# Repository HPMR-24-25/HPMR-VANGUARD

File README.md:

# HPMR KiCad Flight Computer Project

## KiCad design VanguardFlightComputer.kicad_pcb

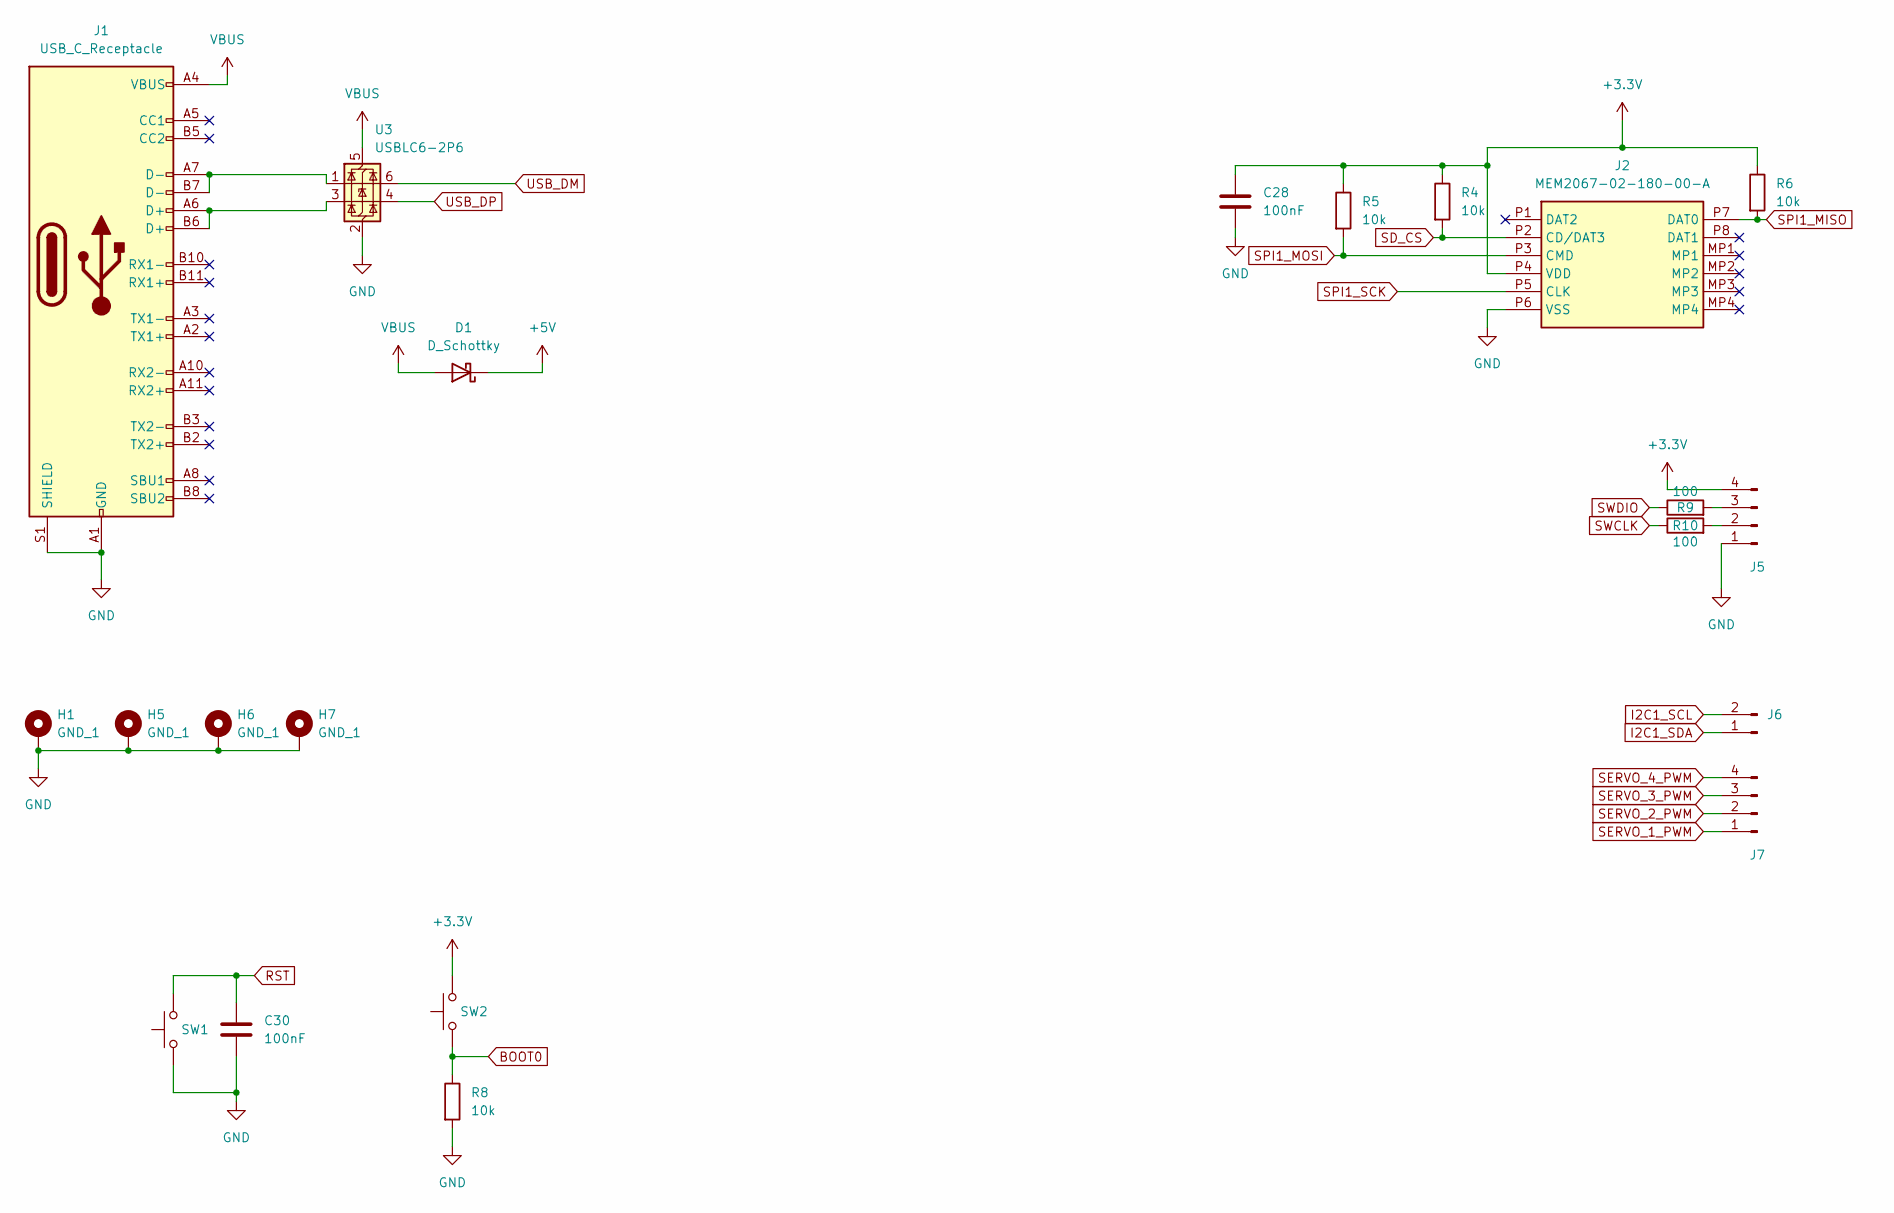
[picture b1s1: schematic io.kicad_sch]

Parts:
C28, C30: 100nF; C_0402_1005Metric
D1: D_Schottky; D_0402_1005Metric
H1, H5, H6, H7: GND_1; MountingHole_2.2mm_M2_DIN965_Pad_TopBottom
J1: USB_C_Receptacle; USB_C_Receptacle_Molex_105450-0101
J2: MEM2067-02-180-00-A; MEM20670218000A; Manufacturer_Part_Number MEM2067-02-180-00-A; Mouser Part Number 640-MEM20670218000A
J5, J7: Conn_01x04_Pin; PinSocket_1x04_P2.54mm_Vertical
J6: Conn_01x02_Pin; PinHeader_1x02_P2.54mm_Vertical
R4, R5, R6, R8: 10k; R_0402_1005Metric
R9, R10: 100; R_0402_1005Metric
SW1, SW2: SW_Push; SW_SPST_PTS810
U3: USBLC6-2P6; SOT-666

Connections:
+3.3V: C28.1, J2.P4 (VDD), J5.4, R4.1, R5.1, R6.1, SW2.2; also elsewhere on the board
+5V: D1.1 (K); also elsewhere on the board
BOOT0: R8.1, SW2.1; also elsewhere on the board
GND: C28.2, C30.2, H1.MP, H5.MP, H6.MP, H7.MP, J1.A1 (GND), J1.A12 (GND), J1.B1 (GND), J1.B12 (GND), J1.S1 (SHIELD), J2.P6 (VSS), J5.1, R8.2, SW1.1, U3.2 (GND); also elsewhere on the board
I2C1_SCL: J6.2; also elsewhere on the board
I2C1_SDA: J6.1; also elsewhere on the board
unnamed: J1.A6 (D+), J1.B6 (D+), U3.3 (I/O2)
unnamed: J1.A7 (D-), J1.B7 (D-), U3.1 (I/O1)
unnamed: J5.2, R10.2
unnamed: J5.3, R9.2
RST: C30.1, SW1.2; also elsewhere on the board
SD_CS: J2.P2 (CD/DAT3), R4.2; also elsewhere on the board
SERVO_1_PWM: J7.1; also elsewhere on the board
SERVO_2_PWM: J7.2; also elsewhere on the board
SERVO_3_PWM: J7.3; also elsewhere on the board
SERVO_4_PWM: J7.4; also elsewhere on the board
SPI1_MISO: J2.P7 (DAT0), R6.2; also elsewhere on the board
SPI1_MOSI: J2.P3 (CMD), R5.2; also elsewhere on the board
SPI1_SCK: J2.P5 (CLK); also elsewhere on the board
SWCLK: R10.1; also elsewhere on the board
SWDIO: R9.1; also elsewhere on the board
USB_DM: U3.6 (I/O1); also elsewhere on the board
USB_DP: U3.4 (I/O2); also elsewhere on the board
VBUS: D1.2 (A), J1.A4 (VBUS), J1.A9 (VBUS), J1.B4 (VBUS), J1.B9 (VBUS), U3.5 (VBUS)

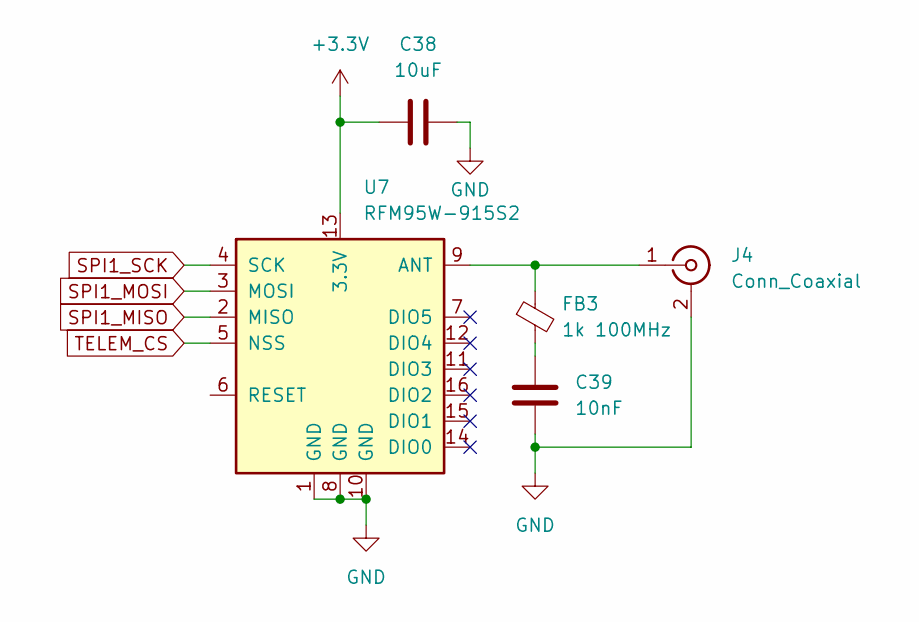
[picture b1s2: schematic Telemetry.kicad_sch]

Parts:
C38: 10uF; C_0402_1005Metric
C39: 10nF; C_0402_1005Metric
FB3: 1k 100MHz; C_0603_1608Metric
J4: Conn_Coaxial; U.FL_Hirose_U.FL-R-SMT-1_Vertical
U7: RFM95W-915S2; HOPERF_RFM9XW_SMD

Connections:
+3.3V: C38.1, U7.13 (3.3V); also elsewhere on the board
GND: C38.2, C39.2, J4.2 (Ext), U7.1 (GND), U7.8 (GND), U7.10 (GND); also elsewhere on the board
unnamed: C39.1, FB3.2
unnamed: FB3.1, J4.1 (In), U7.9 (ANT)
SPI1_MISO: U7.2 (MISO); also elsewhere on the board
SPI1_MOSI: U7.3 (MOSI); also elsewhere on the board
SPI1_SCK: U7.4 (SCK); also elsewhere on the board
TELEM_CS: U7.5 (NSS); also elsewhere on the board

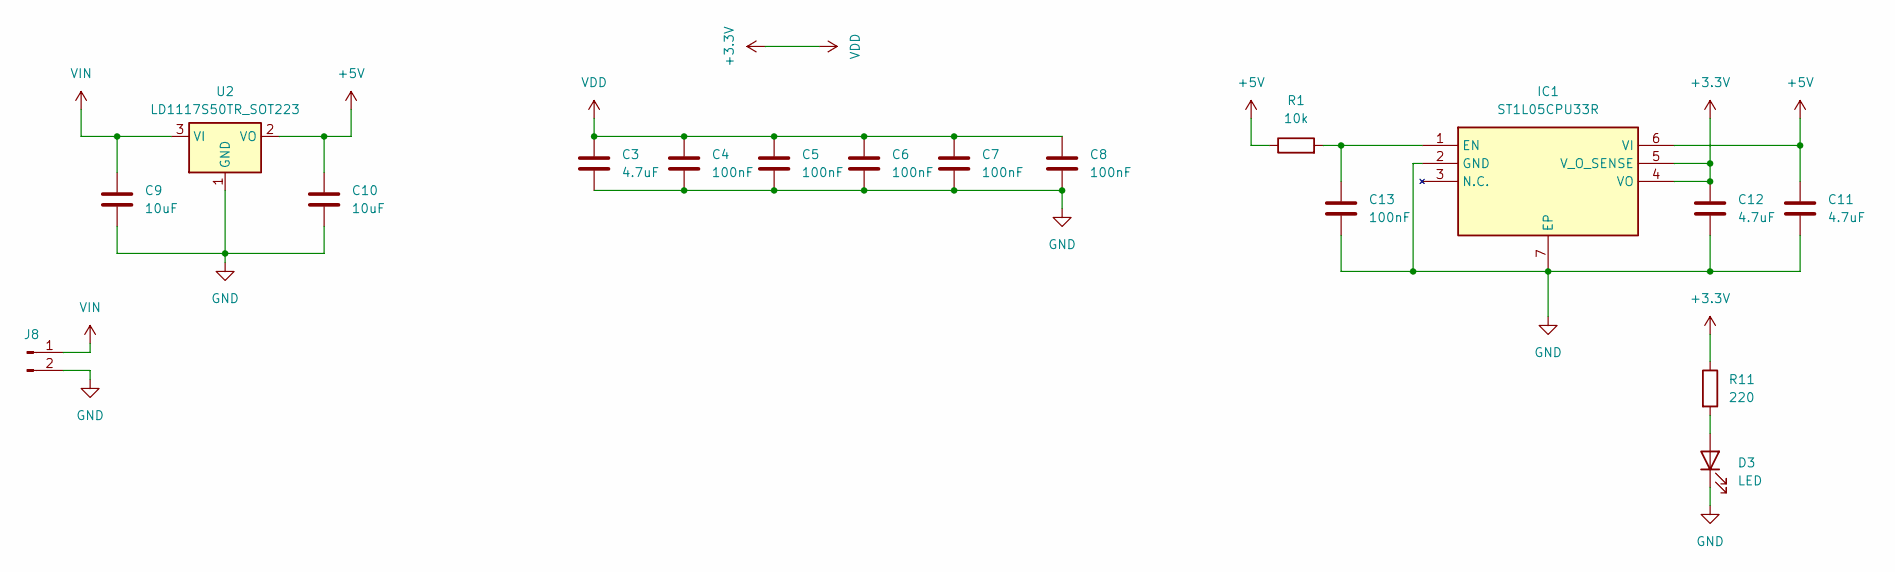
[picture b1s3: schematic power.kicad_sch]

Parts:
C3, C11, C12: 4.7uF; C_0402_1005Metric
C4, C5, C6, C7, C8, C13: 100nF; C_0402_1005Metric
C9, C10: 10uF; C_0603_1608Metric
D3: LED; LED_0603_1608Metric
IC1: ST1L05CPU33R; SON95P300X300X100-7N-D; Manufacturer_Part_Number ST1L05CPU33R; Mouser Part Number 511-ST1L05CPU33R
J8: Conn_01x02_Pin; PinHeader_1x02_P2.54mm_Vertical
R1: 10k; R_0603_1608Metric
R11: 220; R_0402_1005Metric
U2: LD1117S50TR_SOT223; SOT-223-3_TabPin2

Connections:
+3.3V: C3.1, C4.1, C5.1, C6.1, C7.1, C8.1, C12.1, IC1.4 (VO), IC1.5 (V_O_SENSE), R11.1; also elsewhere on the board
+5V: C10.1, C11.1, IC1.6 (VI), R1.1, U2.2 (VO); also elsewhere on the board
GND: C3.2, C4.2, C5.2, C6.2, C7.2, C8.2, C9.2, C10.2, C11.2, C12.2, C13.2, D3.1 (K), IC1.2 (GND), IC1.7 (EP), J8.2, U2.1 (GND); also elsewhere on the board
unnamed: D3.2 (A), R11.2
unnamed: C13.1, IC1.1 (EN), R1.2
VIN: C9.1, J8.1, U2.3 (VI)

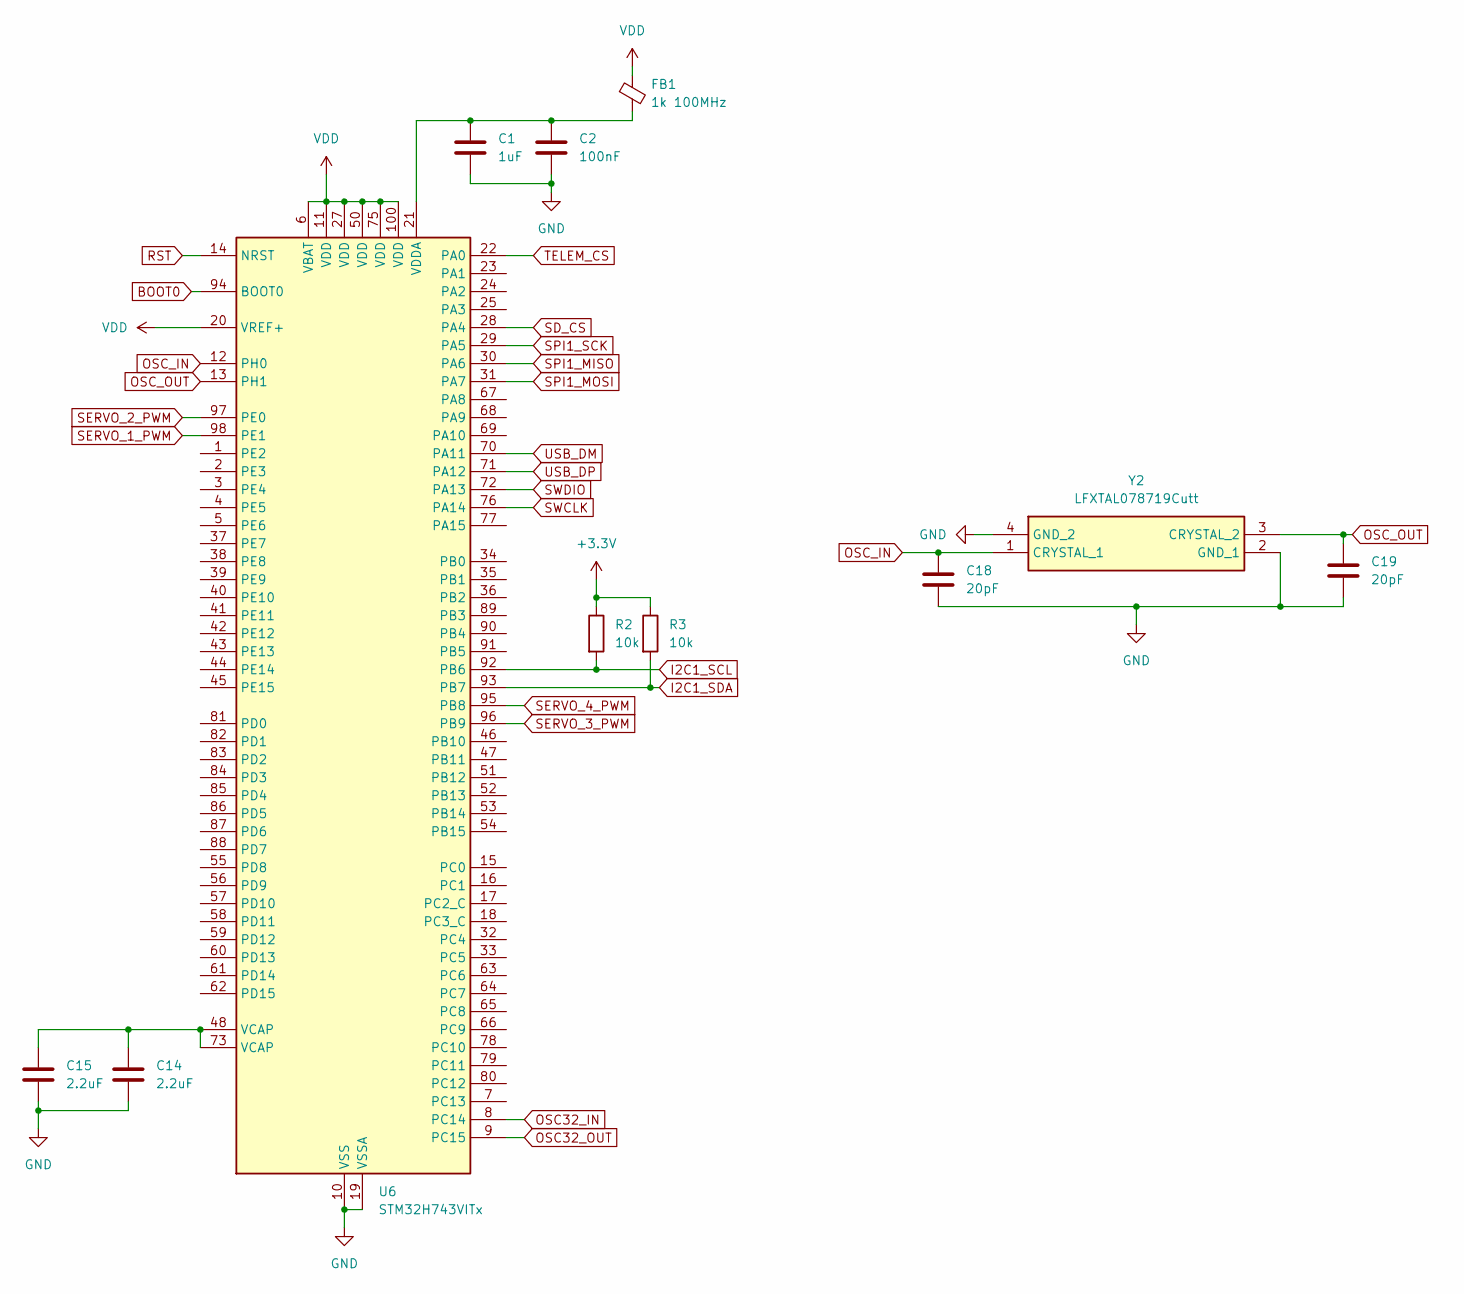
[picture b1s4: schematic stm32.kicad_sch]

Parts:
C1: 1uF; C_0402_1005Metric
C2: 100nF; C_0402_1005Metric
C14, C15: 2.2uF; C_0402_1005Metric
C18, C19: 20pF; C_0402_1005Metric
FB1: 1k 100MHz; C_0603_1608Metric
R2, R3: 10k; R_0402_1005Metric
U6: STM32H743VITx; LQFP-100_14x14mm_P0.5mm
Y2: LFXTAL078719Cutt; Manufacturer_Part_Number LFXTAL078719Cutt; Mouser Part Number 449-LFXTAL078719CUTT

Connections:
+3.3V: FB1.1, R2.1, R3.1, U6.6 (VBAT), U6.11 (VDD), U6.20 (VREF+), U6.27 (VDD), U6.50 (VDD), U6.75 (VDD), U6.100 (VDD); also elsewhere on the board
BOOT0: U6.94 (BOOT0); also elsewhere on the board
GND: C1.2, C2.2, C14.2, C15.2, C18.1, C19.1, U6.10 (VSS), U6.19 (VSSA), U6.26 (VSS), U6.49 (VSS), U6.74 (VSS), U6.99 (VSS), Y2.2 (GND_1), Y2.4 (GND_2); also elsewhere on the board
I2C1_SCL: R2.2, U6.92 (PB6); also elsewhere on the board
I2C1_SDA: R3.2, U6.93 (PB7); also elsewhere on the board
unnamed: C14.1, C15.1, U6.48 (VCAP), U6.73 (VCAP)
unnamed: C1.1, C2.1, FB1.2, U6.21 (VDDA)
OSC32_IN: U6.8 (PC14)
OSC32_OUT: U6.9 (PC15)
OSC_IN: C18.2, U6.12 (PH0), Y2.1 (CRYSTAL_1)
OSC_OUT: C19.2, U6.13 (PH1), Y2.3 (CRYSTAL_2)
RST: U6.14 (NRST); also elsewhere on the board
SD_CS: U6.28 (PA4); also elsewhere on the board
SERVO_1_PWM: U6.98 (PE1); also elsewhere on the board
SERVO_2_PWM: U6.97 (PE0); also elsewhere on the board
SERVO_3_PWM: U6.96 (PB9); also elsewhere on the board
SERVO_4_PWM: U6.95 (PB8); also elsewhere on the board
SPI1_MISO: U6.30 (PA6); also elsewhere on the board
SPI1_MOSI: U6.31 (PA7); also elsewhere on the board
SPI1_SCK: U6.29 (PA5); also elsewhere on the board
SWCLK: U6.76 (PA14); also elsewhere on the board
SWDIO: U6.72 (PA13); also elsewhere on the board
TELEM_CS: U6.22 (PA0); also elsewhere on the board
USB_DM: U6.70 (PA11); also elsewhere on the board
USB_DP: U6.71 (PA12); also elsewhere on the board

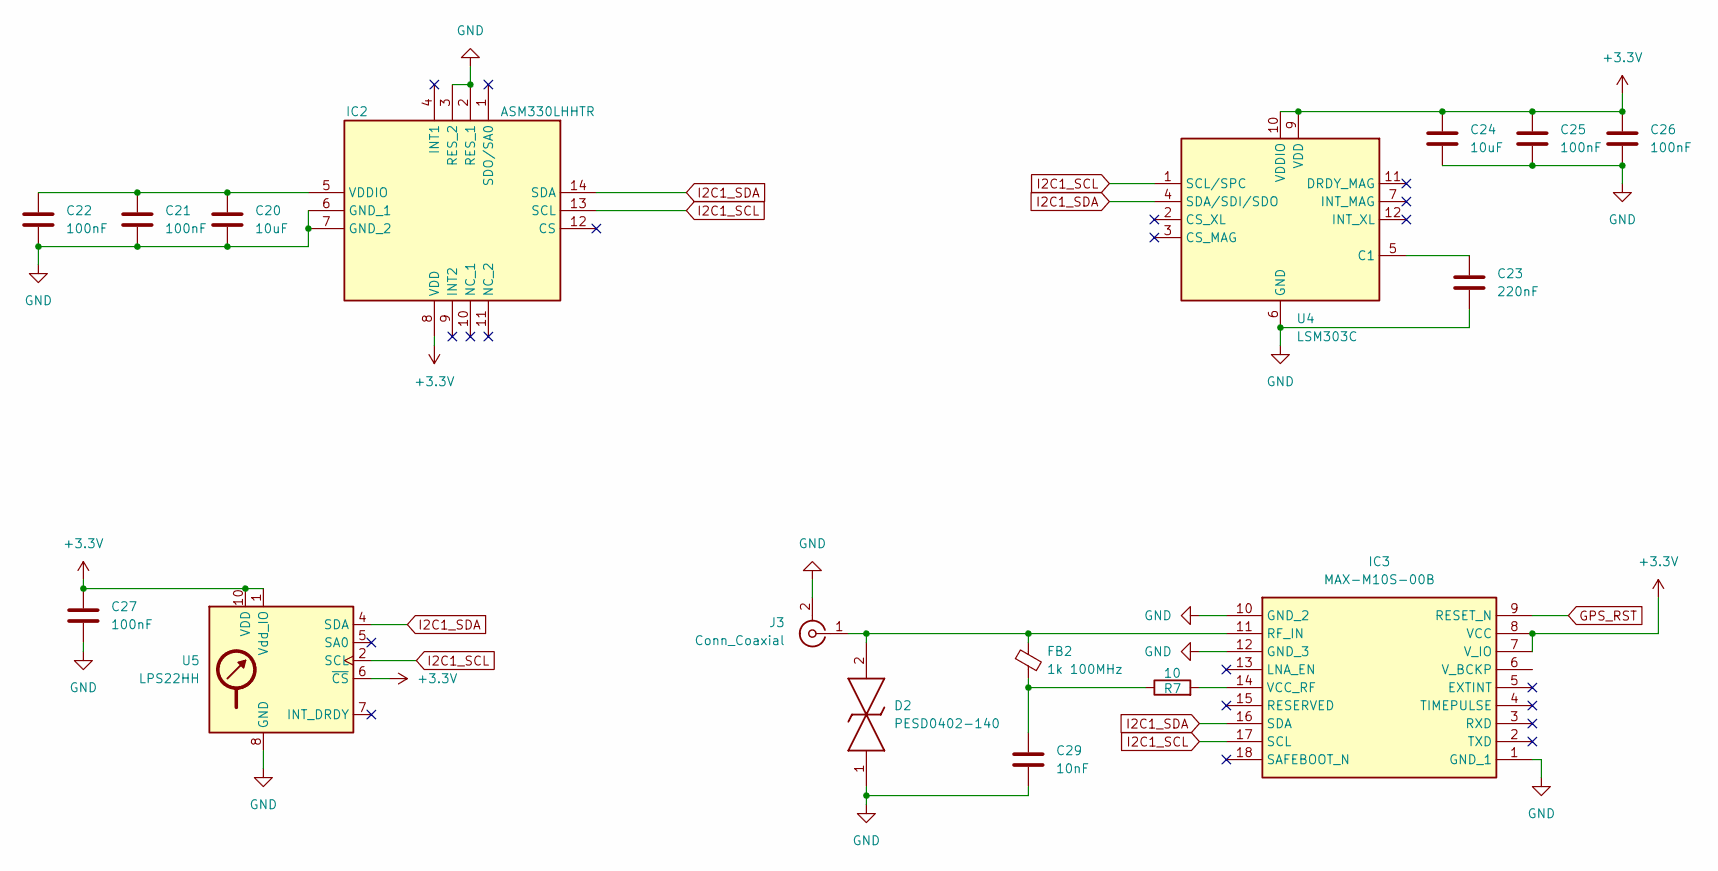
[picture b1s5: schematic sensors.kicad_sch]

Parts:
C20, C24: 10uF; C_0402_1005Metric
C21, C22, C25, C26, C27: 100nF; C_0402_1005Metric
C23: 220nF; C_0402_1005Metric
C29: 10nF; C_0402_1005Metric
D2: PESD0402-140; DIONC1005X43N; Mouser Part Number 650-PESD0402-140
FB2: 1k 100MHz; C_0603_1608Metric
IC2: ASM330LHHTR; LSM6DS3USTR; Manufacturer_Part_Number ASM330LHHTR; Mouser Part Number 511-ASM330LHHTR
IC3: MAX-M10S-00B; MAXM10S00B; Mouser Part Number 377-MAX-M10S-00B
J3: Conn_Coaxial; U.FL_Hirose_U.FL-R-SMT-1_Vertical
R7: 10; C_0402_1005Metric
U4: LSM303C; LGA-12_2x2mm_P0.5mm
U5: LPS22HH; ST_HLGA-10_2x2mm_P0.5mm_LayoutBorder3x2y

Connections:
+3.3V: C24.1, C25.1, C26.1, C27.1, IC2.8 (VDD), IC3.7 (V_IO), IC3.8 (VCC), U4.9 (VDD), U4.10 (VDDIO), U5.1 (Vdd_IO), U5.6 (~CS), U5.10 (VDD); also elsewhere on the board
GND: C20.2, C21.2, C22.2, C23.2, C24.2, C25.2, C26.2, C27.2, C29.2, D2.1, IC2.2 (RES_1), IC2.3 (RES_2), IC2.6 (GND_1), IC2.7 (GND_2), IC3.1 (GND_1), IC3.10 (GND_2), IC3.12 (GND_3), J3.2 (Ext), U4.6 (GND), U4.8 (GND), U5.3 (GND), U5.8 (GND), U5.9 (GND); also elsewhere on the board
GPS_RST: IC3.9 (RESET_N)
I2C1_SCL: IC2.13 (SCL), IC3.17 (SCL), U4.1 (SCL/SPC), U5.2 (SCL); also elsewhere on the board
I2C1_SDA: IC2.14 (SDA), IC3.16 (SDA), U4.4 (SDA/SDI/SDO), U5.4 (SDA); also elsewhere on the board
unnamed: C29.1, FB2.2, R7.1
unnamed: C20.1, C21.1, C22.1, IC2.5 (VDDIO)
unnamed: D2.2, FB2.1, IC3.11 (RF_IN), J3.1 (In)
unnamed: IC3.14 (VCC_RF), R7.2
unnamed: C23.1, U4.5 (C1)

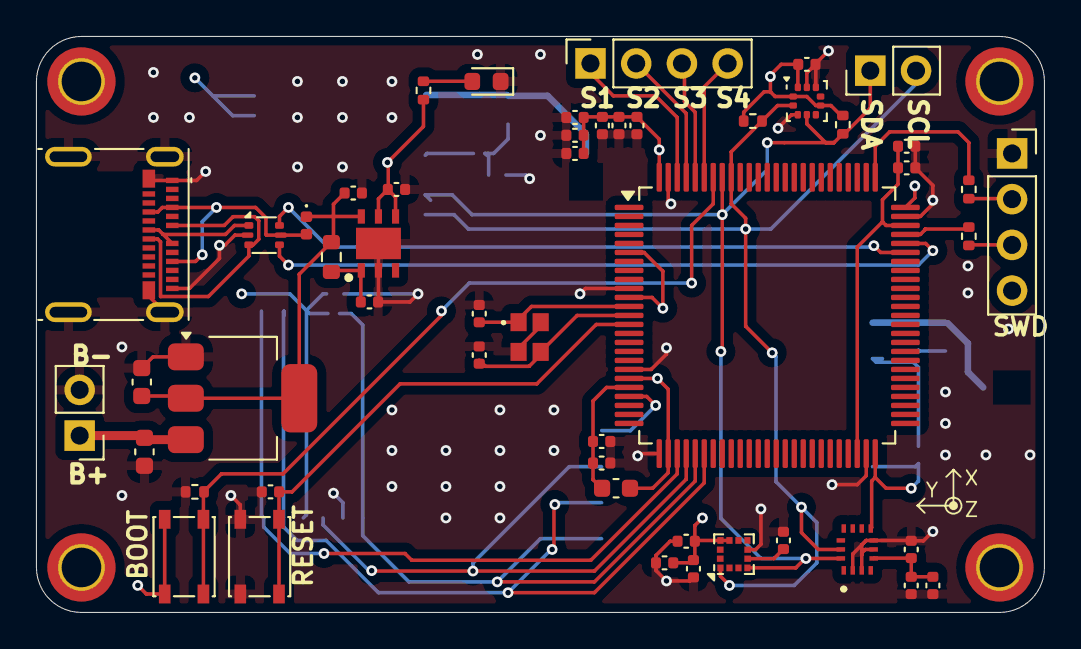
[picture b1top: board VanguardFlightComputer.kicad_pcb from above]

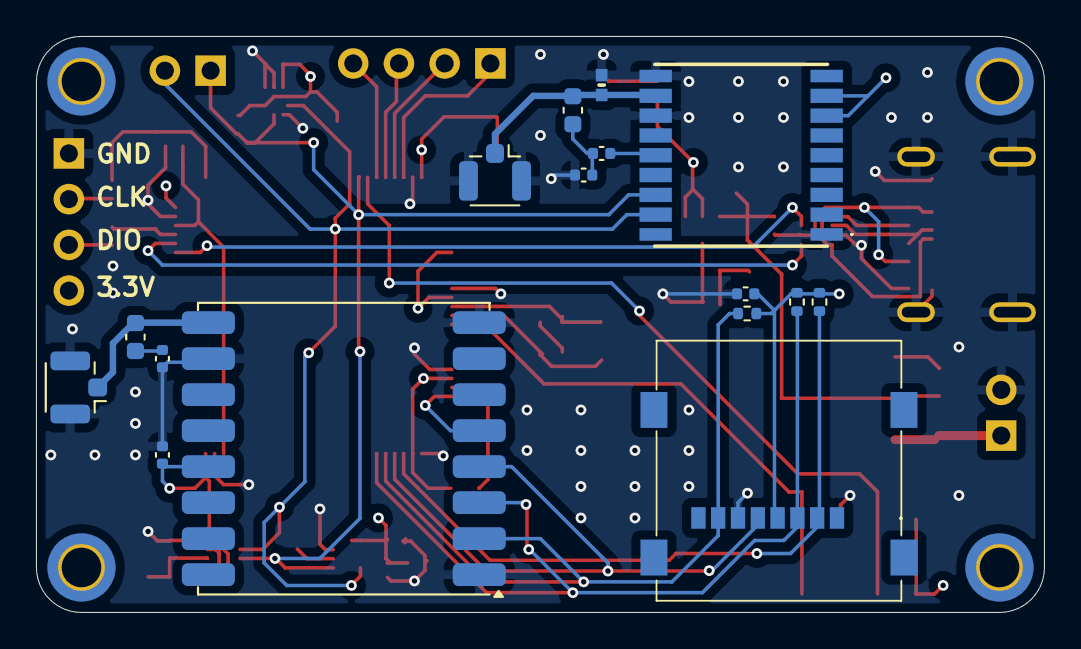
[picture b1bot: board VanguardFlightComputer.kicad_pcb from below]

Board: 4 copper layers, 56.0 x 32.0 mm, 71 parts (16 on the bottom side), 39 nets.

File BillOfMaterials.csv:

Reference,Value,Datasheet,Footprint,Qty,DNP
C1,1uF,~,Capacitor_SMD:C_0402_1005Metric,1,
"C2,C4,C5,C6,C7,C8,C13,C21,C22,C25,C26,C27,C28,C30",0.1uF,~,Capacitor_SMD:C_0402_1005Metric,13,
"C3,C11,C12",4.7uF,~,Capacitor_SMD:C_0402_1005Metric,3,
"C9,C10",10uF,~,Capacitor_SMD:C_0603_1608Metric,2,
"C14,C15",2.2uF,~,Capacitor_SMD:C_0402_1005Metric,2,
"C18,C19",20pF,~,Capacitor_SMD:C_0402_1005Metric,2,
"C20,C24,C38",10uF,~,Capacitor_SMD:C_0402_1005Metric,3,
C23,0.22uF,~,Capacitor_SMD:C_0402_1005Metric,1,
"C29,C39",10nF,~,Capacitor_SMD:C_0402_1005Metric,2,
D1,D_Schottky,~,Diode_SMD:D_0402_1005Metric,1,
D2,PESD0402-140,https://www.littelfuse.com/~/media/electronics/product_speci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,VanguardLib:DIONC1005X43N,1,
"FB1,FB2,FB3",1k 100MHz,https://www.mouser.com/datasheet/2/281/ENFA0004-1915711.pdf,Capacitor_SMD:C_0603_1608Metric,3,
IC1,ST1L05CPU33R,https://www.mouser.de/datasheet/2/389/st1l05-974244.pdf,VanguardLib:SON95P300X300X100-7N-D,1,
IC2,ASM330LHHTR,https://www.st.com/resource/en/datasheet/asm330lhh.pdf,VanguardLib:LSM6DS3USTR,1,
IC3,MAX-M10S-00B,https://content.u-blox.com/sites/default/files/MAX-M10S_Inte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,VanguardLib:MAXM10S00B,1,
J1,USB_C_Receptacle,https://www.usb.org/sites/default/files/documents/usb_type-c.zip,Connector_USB:USB_C_Receptacle_Molex_105450-0101,1,
J2,MEM2067-02-180-00-A,https://gct.co/files/drawings/mem2067.pdf,VanguardLib:MEM20670218000A,1,
"J3,J4",Conn_Coaxial,~,Connector_Coaxial:U.FL_Hirose_U.FL-R-SMT-1_Vertical,2,
"J5,J7",Conn_01x04_Pin,~,Connector_PinSocket_2.54mm:PinSocket_1x04_P2.54mm_Vertical,2,
"J6,J8",Conn_01x02_Pin,~,Connector_PinHeader_2.54mm:PinHeader_1x02_P2.54mm_Vertical,2,
R1,10k,~,Resistor_SMD:R_0603_1608Metric,1,
"R2,R3,R4,R5,R6,R8",10k,~,Resistor_SMD:R_0402_1005Metric,6,
R7,10,~,Capacitor_SMD:C_0402_1005Metric,1,
"R9,R10",100,~,Resistor_SMD:R_0402_1005Metric,2,
R11,220,~,Resistor_SMD:R_0402_1005Metric,1,
D3,LED_RED,~,LED_SMD:LED_0603_1608Metric,1,
"SW1,SW2",SW_Push,~,Button_Switch_SMD:SW_SPST_PTS810,2,
U2,LD1117S50TR_SOT223,http://www.st.com/st-web-ui/static/active/en/resource/techni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,Package_TO_SOT_SMD:SOT-223-3_TabPin2,1,
U3,USBLC6-2P6,https://www.st.com/resource/en/datasheet/usblc6-2.pdf,Package_TO_SOT_SMD:SOT-666,1,
U4,LSM303C,www.st.com/resource/en/datasheet/lsm303c.pdf,Package_LGA:LGA-12_2x2mm_P0.5mm,1,
U5,LPS22HH,https://www.st.com/resource/en/datasheet/lps22hh.pdf,Package_LGA:ST_HLGA-10_2x2mm_P0.5mm_LayoutBorder3x2y,1,
U6,STM32H743VITx,https://www.st.com/resource/en/datasheet/stm32h743vi.pdf,Package_QFP:LQFP-100_14x14mm_P0.5mm,1,
U7,RFM95W-915S2,https://www.hoperf.com/data/upload/portal/20181127/5bfcbea20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,RF_Module:HOPERF_RFM9XW_SMD,1,
Y2,LFXTAL078719Cutt,https://www.mouser.de/datasheet/2/741/LFXTAL078719Cutt-1623884.pdf,VanguardLib:LFXTAL078719Cutt,1,

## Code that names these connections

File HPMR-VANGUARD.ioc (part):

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Mcu.Name=STM32H743VITx
Mcu.Package=LQFP100
Mcu.UserName=STM32H743VITx
PA0.Signal=GPIO_Output
PA10.Mode=OTG/Dual_Role_Device
PA10.Signal=USB_OTG_FS_ID
PA11.Mode=OTG/Dual_Role_Device
PA11.Signal=USB_OTG_FS_DM
PA12.Mode=OTG/Dual_Role_Device
PA12.Signal=USB_OTG_FS_DP
PA13\ (JTMS/SWDIO).Signal=DEBUG_JTMS-SWDIO
PA14\ (JTCK/SWCLK).Signal=DEBUG_JTCK-SWCLK
PA4.Signal=GPIO_Output
PA5.Mode=Full_Duplex_Master
PA5.Signal=SPI1_SCK
PA6.Mode=Full_Duplex_Master
PA6.Signal=SPI1_MISO
PA7.Mode=Full_Duplex_Master
PA7.Signal=SPI1_MOSI
PB6.Mode=I2C
PB6.Signal=I2C1_SCL
PB7.Mode=I2C
PB7.Signal=I2C1_SDA
PB8.Signal=GPIO_Output
PB9.Signal=GPIO_Output
PE0.Signal=GPIO_Output
PE1.Signal=GPIO_Output
PH0-OSC_IN\ (PH0).Mode=HSE-External-Oscillator
PH0-OSC_IN\ (PH0).Signal=RCC_OSC_IN
PH1-OSC_OUT\ (PH1).Mode=HSE-External-Oscillator
PH1-OSC_OUT\ (PH1).Signal=RCC_OSC_OUT
RCC.SYSCLKFreq_VALUE=64000000
board=custom

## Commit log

2024-11-03 Added initial project
2024-11-03 Added all sensors and telemetry modem
2024-11-03 Fixed ground pour
2024-11-04 Added IO
2024-11-05 Change 0201 to 0403
2024-11-08 Re-Routed PCB
2024-11-11 Impedence match trace
2024-11-11 Added STM32_MX Project, LED, Fixed DRC Violations
2024-11-11 Aligned IMU axes and fixed JLC match trace
